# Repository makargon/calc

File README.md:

# Схема полного сумматора для изучения принципов работы алгебры логики в школе

Выполнено на транзисторах 2N2222 и резисторах по 1k и 10k. Схемы можно подключать последовательно. А так же, для удобства рекомендуется вывести элементы управления и индикации.

### Сборка

Разрабатывалось в EasyEDA, а после экспортировано в KiCAD

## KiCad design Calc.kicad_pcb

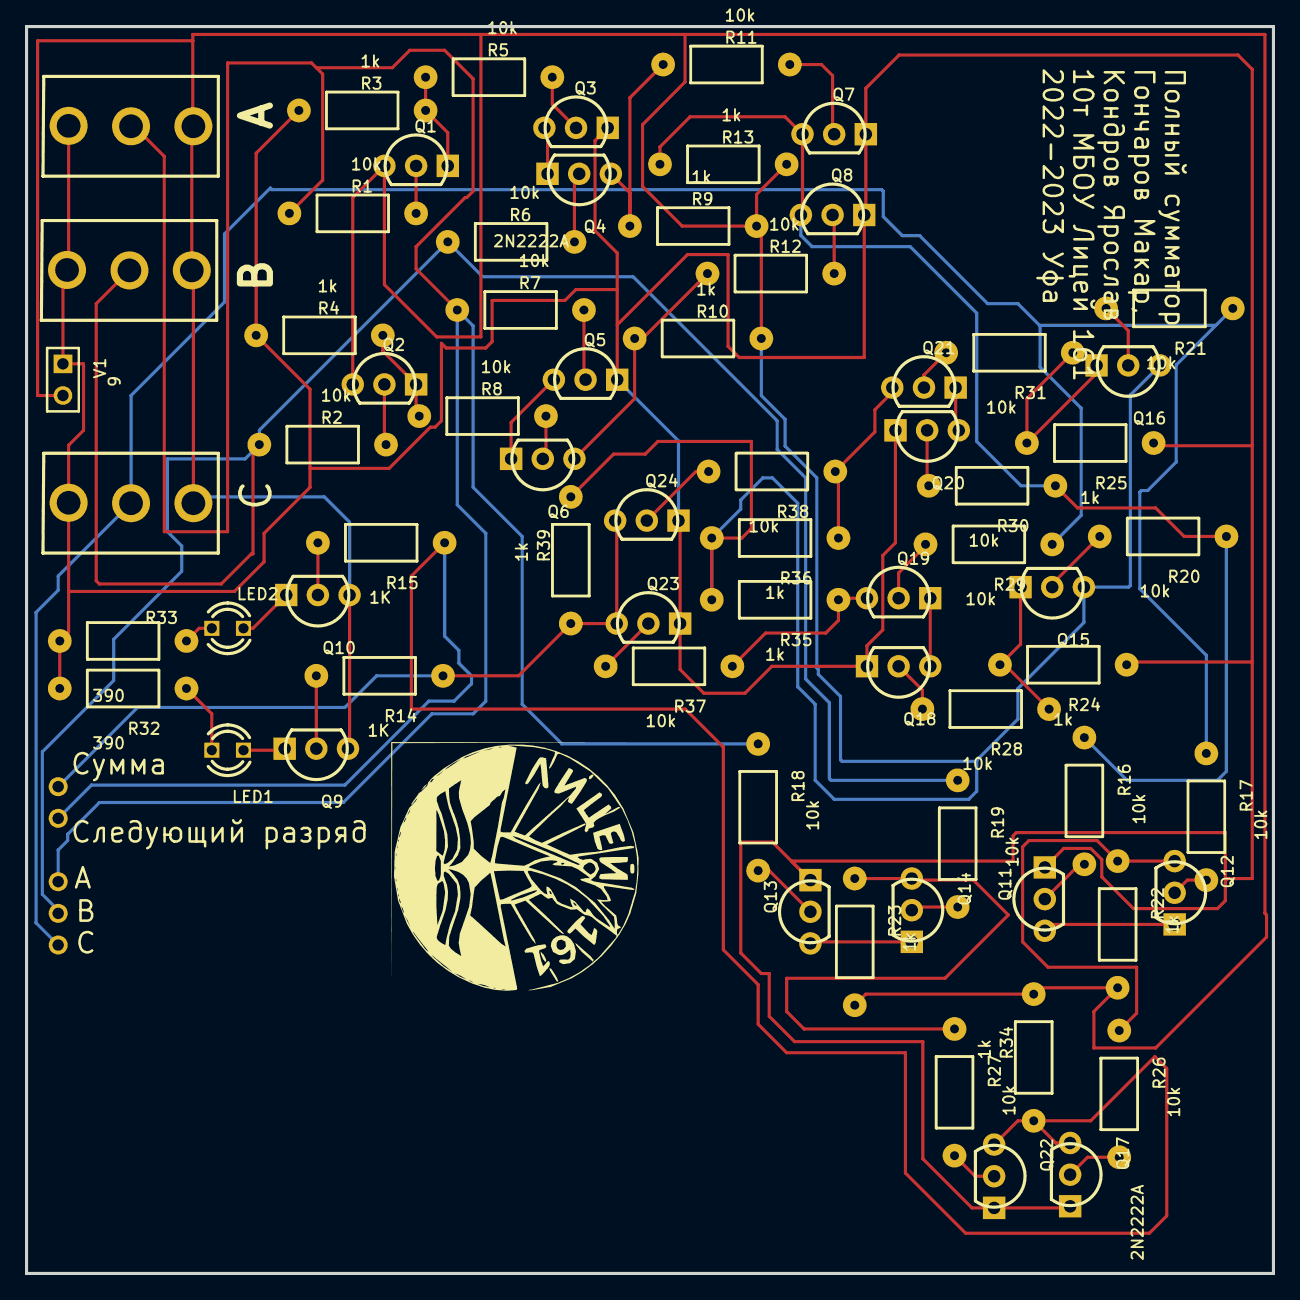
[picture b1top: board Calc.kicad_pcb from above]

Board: 2 copper layers, 100.0 x 100.0 mm, 74 parts (0 on the bottom side), 52 nets.

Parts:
A: MTS-102; MTS-102-A2-ON-ON
B: MTS-102; MTS-102-A2-ON-ON
C: MTS-102; MTS-102-A2-ON-ON
LED1, LED2: LED_3mm; LED_LED3MM
Pad_gge23: Pad_gge23
Pad_gge41: Pad_gge41
Pad_gge140: Pad_gge140
Pad_gge167: Pad_gge167
Pad_gge194: Pad_gge194
Q1, Q2, Q3, Q4, Q5, Q6, Q7, Q8, Q9, Q10, Q11, Q12, Q13, Q14, Q15, Q16, Q17, Q18, Q19, Q20, Q21, Q22, Q23, Q24: 2N2222A; TO-92-3_L4.8-W3.7-P2.54-R
R1, R2, R5, R6, R7, R8, R11, R12, R16, R17, R18, R19, R20, R21, R26, R27, R28, R29, R30, R31, R37, R38: 10k; RC08
R3, R4, R9, R10, R13, R22, R23, R24, R25, R34, R35, R36, R39: 1k; RC08
R14, R15: 1K; RC08
R32, R33: 390; RC08
V1: 9; HDR1X2

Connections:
A: A.2, Pad_gge140.3, R1.1, R7.1, R18.1
B: B.2, Pad_gge167.4, R2.1, R6.1, R19.1
CININ: C.2, Pad_gge194.5, R17.1, R21.1, R29.1
CINOUT: Pad_gge41.2, Q17.3, Q22.3, R15.1, R34.1
GND: A.3, B.3, C.3, Q1.3, Q2.3, Q9.3, Q10.3, Q15.3, Q16.3, R9.2, R10.2, R13.2, R22.2, R23.2, R34.2, R35.2, R36.2, R39.2, V1.2
LED1_A: LED1.A, Q9.1
LED1_K: LED1.K, R32.1
LED2_A: LED2.A, Q10.1
LED2_K: LED2.K, R33.1
OUT: Pad_gge23.1, Q23.3, Q24.3, R14.1, R39.1
Q2_2: Q2.2, R2.2
Q3_2: Q3.2, R5.2
Q3_3: Q3.3, Q4.1
Q4_2: Q4.2, R6.2
Q6_1: Q5.3, Q6.1
Q9_2: Q9.2, R14.2
Q10_2: Q10.2, R15.2
Q11_2: Q11.2, R16.2
Q11_3: Q11.3, Q12.1
Q12_2: Q12.2, R17.2
Q14_1: Q13.3, Q14.1
Q15_2: Q15.2, R20.2
Q16_1: Q16.1, R25.2, R31.1
Q19_1: Q18.3, Q19.1
Q20_2: Q20.2, R30.2
Q20_3: Q20.3, Q21.1
Q21_2: Q21.2, R31.2
Q21_3: Q21.3, R36.1, R38.1
Q23_2: Q23.2, R37.2
Q24_2: Q24.2, R38.2
R1_2: Q1.2, R1.2
R5_1: Q1.1, R3.2, R5.1
R7_2: Q5.2, R7.2
R8_1: Q2.1, R4.2, R8.1
R8_2: Q6.2, R8.2
R11_1: Q4.3, R9.1, R11.1
R11_2: Q7.2, R11.2
R12_1: Q6.3, R10.1, R12.1
R12_2: Q8.2, R12.2
R13_1: Q7.3, Q8.3, R13.1, R16.1, R20.1, R30.1
R18_2: Q13.2, R18.2
R19_2: Q14.2, R19.2
R21_2: Q16.2, R21.2
R24_2: Q15.1, R24.2, R28.1
R26_1: Q12.3, R22.1, R26.1
R26_2: Q17.2, R26.2
R27_1: Q14.3, R23.1, R27.1
R27_2: Q22.2, R27.2
R28_2: Q18.2, R28.2
R29_2: Q19.2, R29.2
R35_1: Q19.3, R35.1, R37.1
VCC: A.1, B.1, C.1, Q3.1, Q5.1, Q7.1, Q8.1, Q11.1, Q13.1, Q17.1, Q18.1, Q20.1, Q22.1, Q23.1, Q24.1, R3.1, R4.1, R24.1, R25.1, R32.2, R33.2, V1.1
